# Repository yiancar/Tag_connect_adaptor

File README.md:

# TAG-Connect Adapter
 A simple routing PCB to connect a TAG-Connect cable to different programmers.

 This is designed to use a [TC2030-MCP-NL](http://www.tag-connect.com/TC2030-MCP-NL) cable and route it to:
 * Atmel ISP 10pin programmers such as [USBASP](https://hobbycomponents.com/usb-interface/841-usbasp-avr-programmer-adaptor)
 * [ST-LINK V2 clone programmer](https://www.amazon.co.uk/Youmile-Emulator-Downloader-Programmer-Programming/dp/B07QBLNDPM/ref=sr_1_1?keywords=stlink&qid=1578231027&sr=8-1). Please note that SWIM is at pin 5 and has been [modded](https://lujji.github.io/blog/stlink-clone-trace/) to be SWO.

 The BYPASS DIP switches can be used to disconnect a connection from the TAG cable to the programmer outputs. This way, the INPUT header can route the TAG cable to any device.

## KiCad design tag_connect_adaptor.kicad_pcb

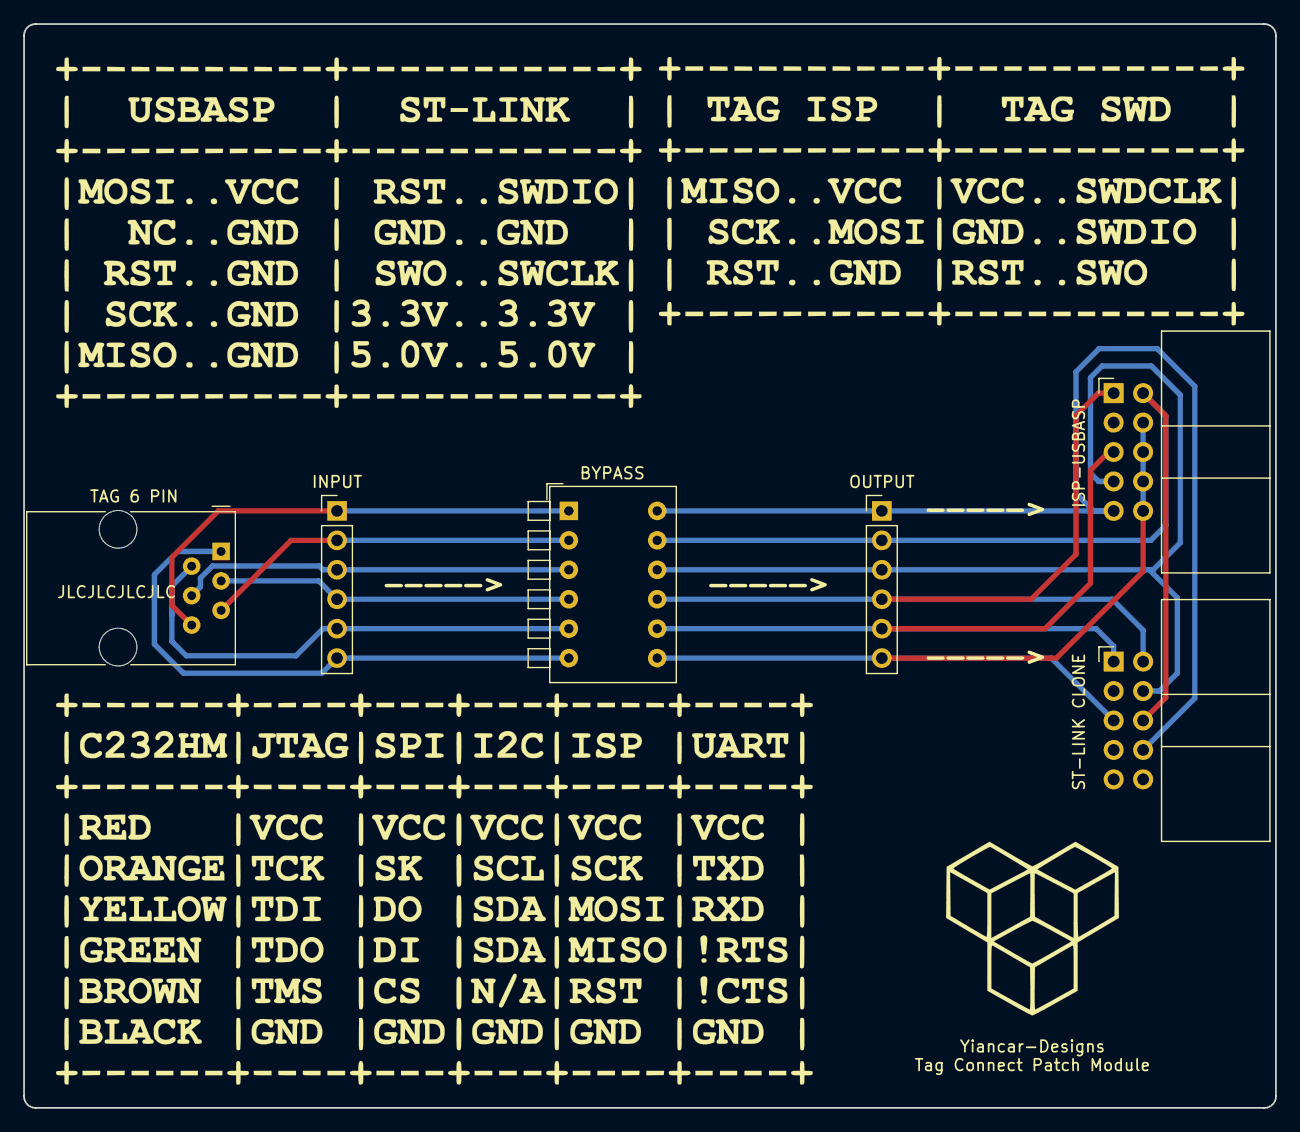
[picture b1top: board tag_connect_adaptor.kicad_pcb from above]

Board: 2 copper layers, 108.0 x 93.5 mm, 6 parts (0 on the bottom side), 12 nets.

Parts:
J1: INPUT; PinHeader_1x06_P2.54mm_Vertical
J2: OUTPUT; PinHeader_1x06_P2.54mm_Vertical
J3: ISP-USBASP; IDC-Header_2x05_P2.54mm_Horizontal
J4: ST-LINK CLONE; IDC-Header_2x05_P2.54mm_Horizontal
J5: TAG 6 PIN; RJ12_Amphenol_54601
SW1: BYPASS; SW_DIP_SPSTx06_Piano_10.8x16.8mm_W7.62mm_P2.54mm

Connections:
/TAG1: J1.1, J5.6, SW1.1
/TAG2: J1.2, J5.5, SW1.2
/TAG3: J1.3, J5.4, SW1.3
/TAG4: J1.4, J5.3, SW1.4
/TAG5: J1.5, J5.2, SW1.5
/TAG6: J1.6, J5.1, SW1.6
/TAG_SW1: J2.1, J3.9, J4.8, SW1.12
/TAG_SW2: J2.2, J3.2, J4.6, SW1.11
/TAG_SW3: J2.3, J3.7, J4.4, SW1.10
/TAG_SW4: J2.4, J3.1, J4.2, SW1.9
/TAG_SW5: J2.5, J3.5, J4.1, SW1.8
/TAG_SW6: J2.6, J3.4, J3.6, J3.8, J3.10, J4.5, SW1.7

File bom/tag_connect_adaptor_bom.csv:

Reference, Quantity, Value, Footprint,Source Link
J1 ,1,INPUT,Connector_PinHeader_2.54mm:PinHeader_1x06_P2.54mm_Vertical,https://lcsc.com/product-detail/Pin-Header-Female-Header_BOO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
J2 ,1,OUTPUT,Connector_PinHeader_2.54mm:PinHeader_1x06_P2.54mm_Vertical,https://lcsc.com/product-detail/Pin-Header-Female-Header_BOO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
J3 ,1,ISP-AVR,Connector_IDC:IDC-Header_2x05_P2.54mm_Horizontal,https://lcsc.com/product-detail/IDC-Connectors_BOOMELE-Boom-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
J4 ,1,ST-LINK CLONE,Connector_IDC:IDC-Header_2x05_P2.54mm_Horizontal,https://lcsc.com/product-detail/IDC-Connectors_BOOMELE-Boom-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
J5 ,1,RJ25,Connector_RJ:RJ12_Amphenol_54601,https://lcsc.com/product-detail/Ethernet-Connectors-Modular-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
SW1 ,1,BYPASS,Button_Switch_THT:SW_DIP_SPSTx06_Piano_10.8x16.8mm_W7.62mm_P2.54mm,https://lcsc.com/product-detail/DIP-Switches_XKB-Enterprise-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

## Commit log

2020-01-05 Licensing
2020-01-05 Readme update
2020-01-05 Generate gerbers
2020-01-06 Numpering update
